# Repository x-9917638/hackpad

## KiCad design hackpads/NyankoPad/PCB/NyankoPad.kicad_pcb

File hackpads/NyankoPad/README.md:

# NyankoPad
NyankoPad (CatPad) is a 8 key, 1 encoder macropad with an OLED display.

## Features
- A two part case that can be 3d printed
- 1 programmable 128x32 OLED display
- 8 Keys
- 1 Rotary encoder
- 3 Built in layers

## Full Render

## Case
Everything fits together using 4 M3 Bolts and heatset inserts.

It has 2 separate printed pieces: Top/Lid and Bottom/Base.

Made in FreeCAD - Had to learn to use this from scratch.

## Schematic

## PCB

## Firmware
QMK is used for the firmware.

Currently, there are 3 layers in the firmware:
- A general layer
- A media layer
- And a workspaces layer.

(These layers will probably not be relevant for you)

The rotary encoder is used to switch layers. 

## BOM
Here should be everything you need to make this hackpad

- 9x Through-hole 1N4148 Diodes
- 8x Cherry MX Switches
- 8x DSA Keycaps
- 1x 0.91in 128x32 OLED display
- 1x Rotary Encoder
- 4x M3x5x4 Heatset inserts
- 4x M3x16mm SHCS Bolts
- 1x XIAO RP2040
- 1x Case (2 printed parts)

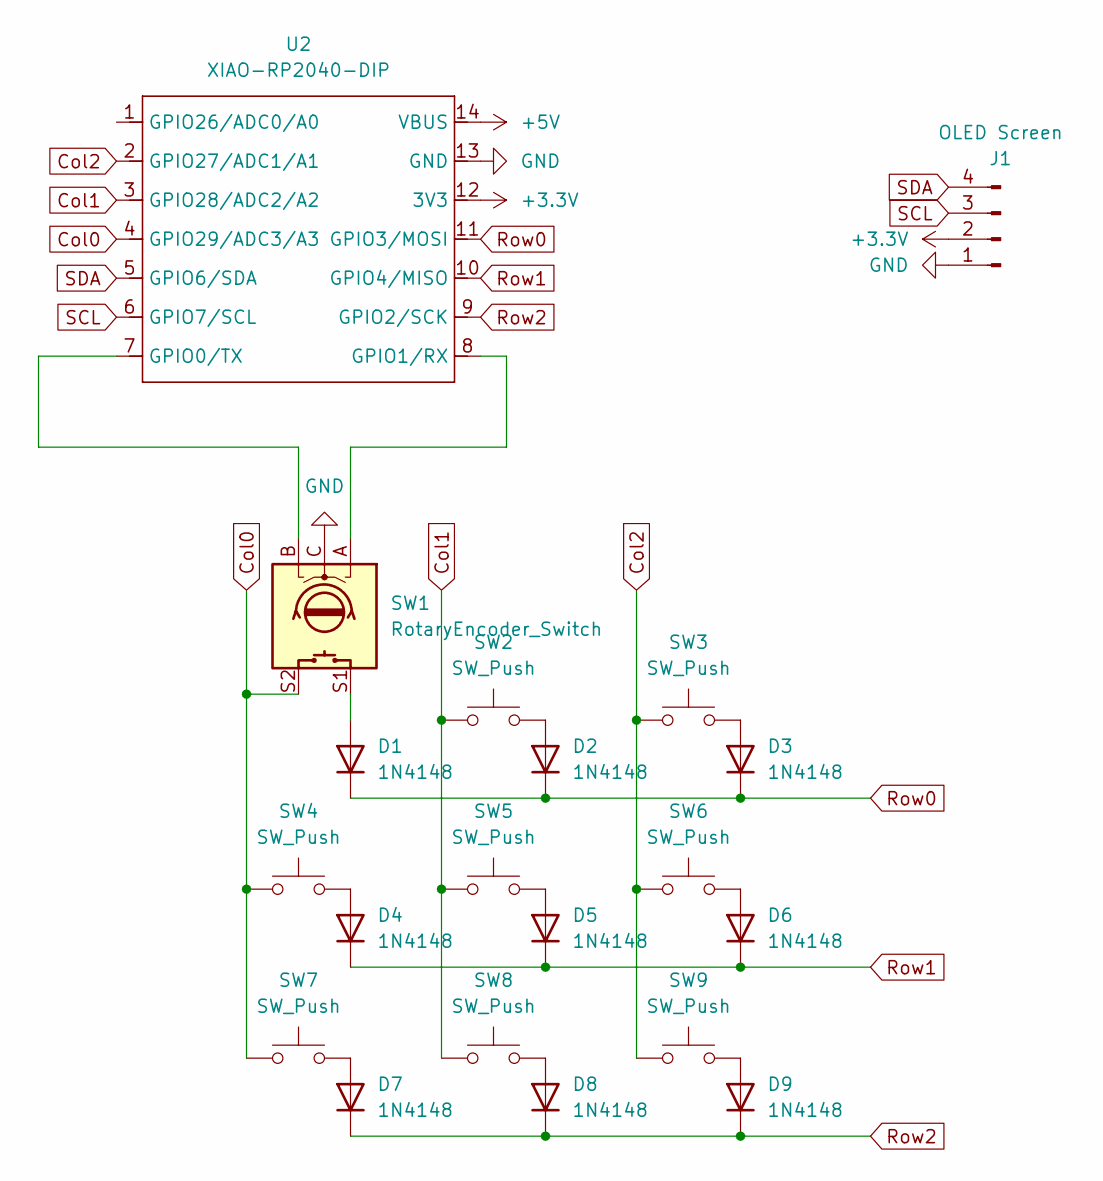
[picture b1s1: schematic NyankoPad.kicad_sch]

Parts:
D1, D2, D3, D4, D5, D6, D7, D8, D9: 1N4148; D_DO-35_SOD27_P7.62mm_Horizontal
J1: OLED Screen; SSD1306-0.91-OLED-4pin-128x32
SW1: RotaryEncoder_Switch; RotaryEncoder_Alps_EC11E-Switch_Vertical_H20mm
SW2, SW3, SW4, SW5, SW6, SW7, SW8, SW9: SW_Push; SW_Cherry_MX_1.00u_PCB
U2: XIAO-RP2040-DIP

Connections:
+3.3V: J1.2, U2.12 (3V3)
+5V: U2.14 (VBUS)
Col0: SW1.S2, SW4.2, SW7.2, U2.4 (GPIO29/ADC3/A3)
Col1: SW2.2, SW5.2, SW8.2, U2.3 (GPIO28/ADC2/A2)
Col2: SW3.2, SW6.2, SW9.2, U2.2 (GPIO27/ADC1/A1)
GND: J1.1, SW1.C, U2.13 (GND)
unnamed: D1.2 (A), SW1.S1
unnamed: D2.2 (A), SW2.1
unnamed: D3.2 (A), SW3.1
unnamed: D4.2 (A), SW4.1
unnamed: D5.2 (A), SW5.1
unnamed: D6.2 (A), SW6.1
unnamed: D7.2 (A), SW7.1
unnamed: D8.2 (A), SW8.1
unnamed: D9.2 (A), SW9.1
unnamed: SW1.B, U2.7 (GPIO0/TX)
unnamed: SW1.A, U2.8 (GPIO1/RX)
Row0: D1.1 (K), D2.1 (K), D3.1 (K), U2.11 (GPIO3/MOSI)
Row1: D4.1 (K), D5.1 (K), D6.1 (K), U2.10 (GPIO4/MISO)
Row2: D7.1 (K), D8.1 (K), D9.1 (K), U2.9 (GPIO2/SCK)
SCL: J1.3, U2.6 (GPIO7/SCL)
SDA: J1.4, U2.5 (GPIO6/SDA)

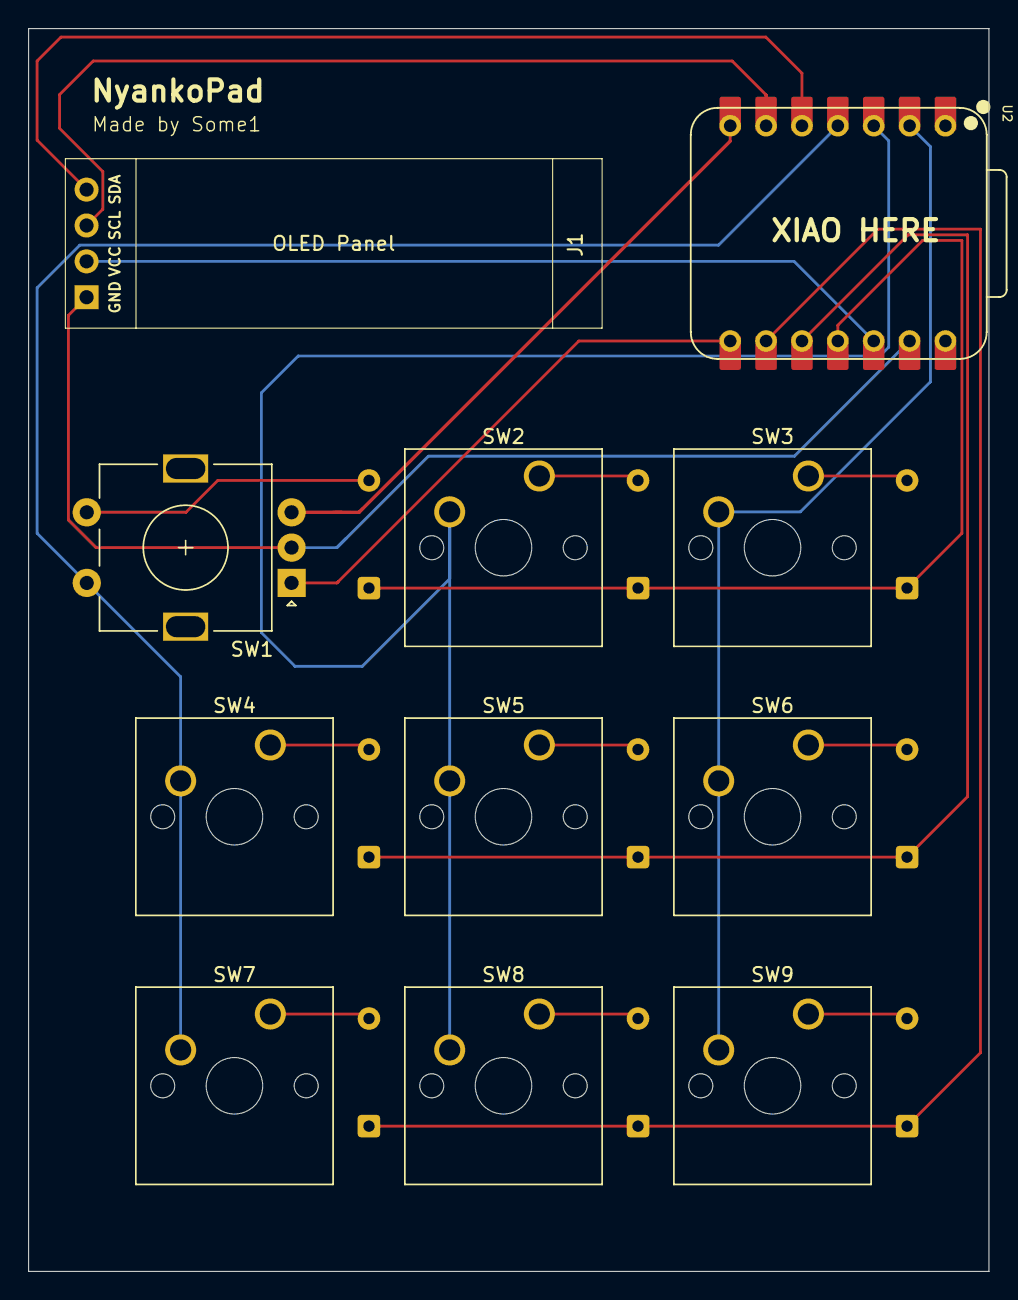
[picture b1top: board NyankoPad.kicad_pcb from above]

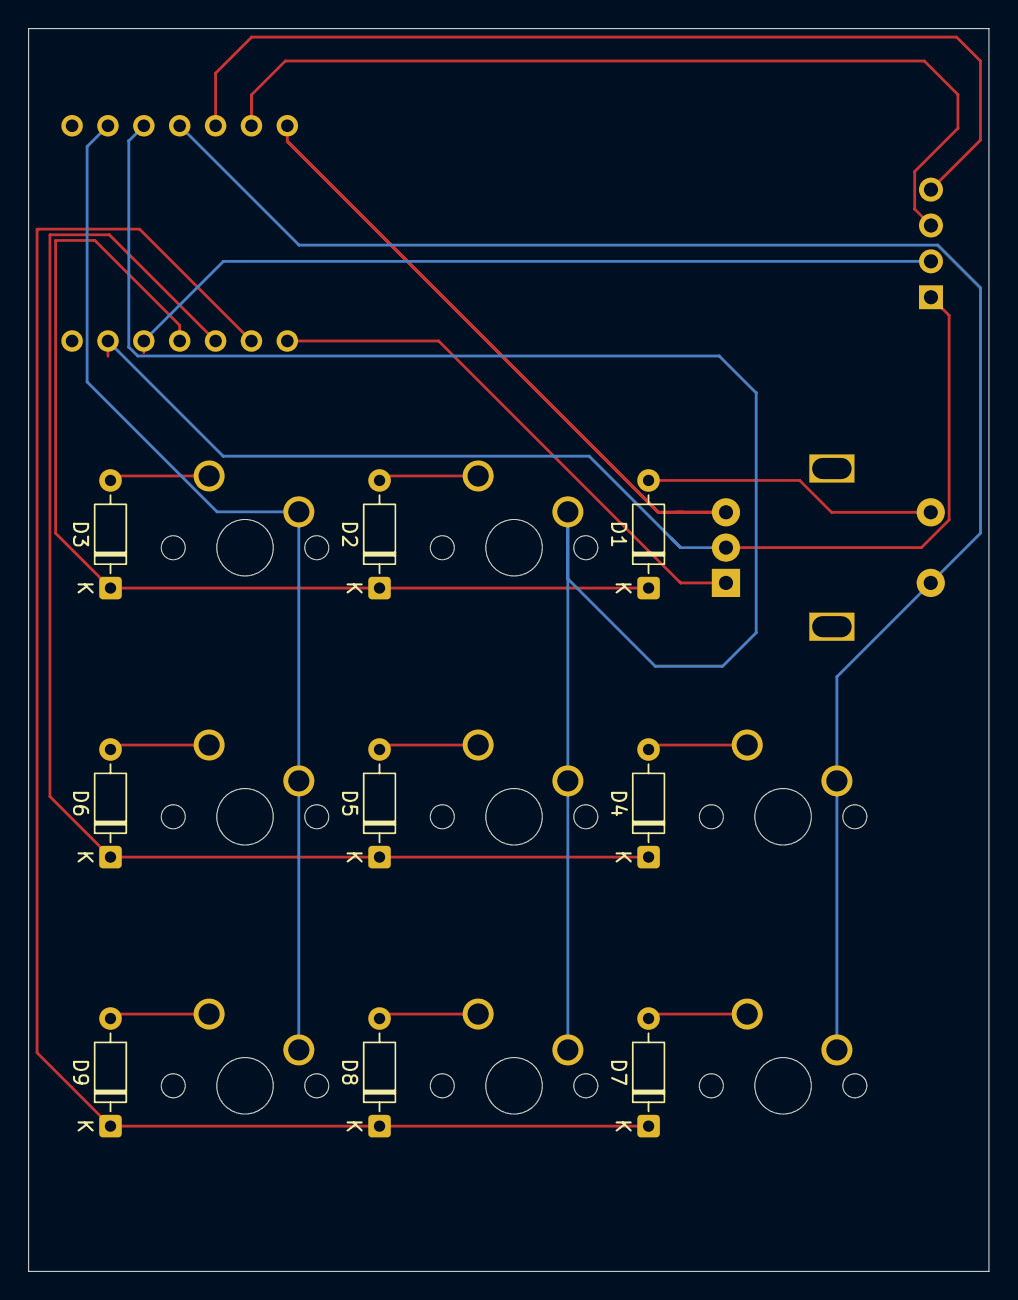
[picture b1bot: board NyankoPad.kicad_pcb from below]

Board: 2 copper layers, 68.0 x 88.0 mm, 20 parts (9 on the bottom side), 21 nets.

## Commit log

2025-07-30 Update CAD files
